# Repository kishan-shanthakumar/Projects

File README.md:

# Projects
The directory name is the tool/topic of the project.

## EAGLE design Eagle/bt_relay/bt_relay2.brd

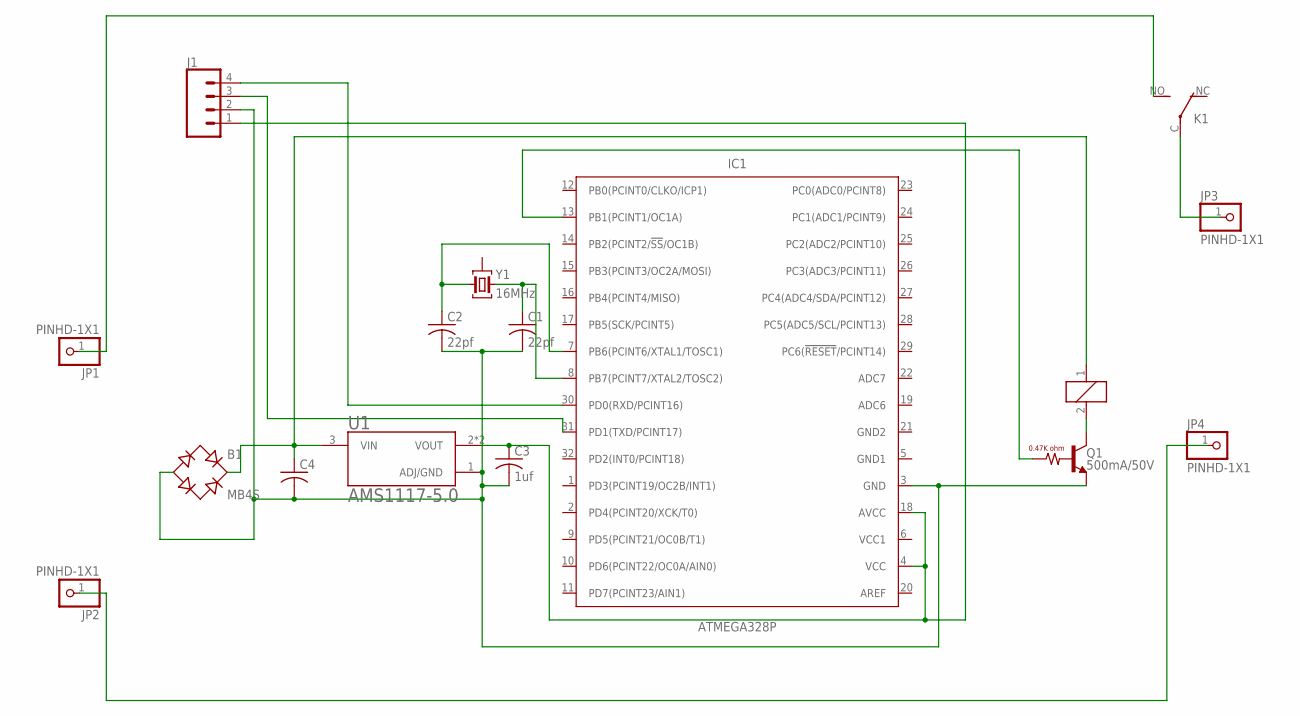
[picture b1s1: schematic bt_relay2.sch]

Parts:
B1: MB4S; SOIC-4
C1, C2: 22pf; C0402
C3: 1uf; C0402
C4: C-USC0402; C0402
IC1: ATMEGA328P; QFN50P500X500X90-33T310N
J1: CONN_04; 1X04
JP1, JP2, JP3, JP4: PINHD-1X1; 1X01
K1: CP1SA-12V; CP1SA
Q1: 500mA/50V; SOT23-3
U1: AMS1117-5.0; SOT229P700X180-4N
Y1: 16MHz; CRYSTAL_CMR200TB

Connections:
AREF: IC1.20 (AREF)
unnamed: C3.1, IC1.4 (VCC), IC1.18 (AVCC), J1.1, U1.2 (VOUT), U1.4 (VOUT)
unnamed: B1.-, C1.2, C2.2, C3.2, C4.2, IC1.3 (GND), J1.2, Q1.2 (E), U1.1 (ADJ/GND)
unnamed: B1.+, C4.1, K1.1, U1.3 (VIN)
unnamed: K1.2, Q1.3 (C)
unnamed: C2.1, IC1.7 (PB6(PCINT6/XTAL1/TOSC1)), Y1.1
unnamed: C1.1, IC1.8 (PB7(PCINT7/XTAL2/TOSC2)), Y1.2
unnamed: IC1.13 (PB1(PCINT1/OC1A)), Q1.1 (B)
unnamed: JP3.1, K1.C
unnamed: JP1.1, K1.NO (S)
unnamed: JP2.1, JP4.1
unnamed: IC1.30 (PD0(RXD/PCINT16)), J1.4
unnamed: IC1.31 (PD1(TXD/PCINT17)), J1.3
VCC1: IC1.6 (VCC1)

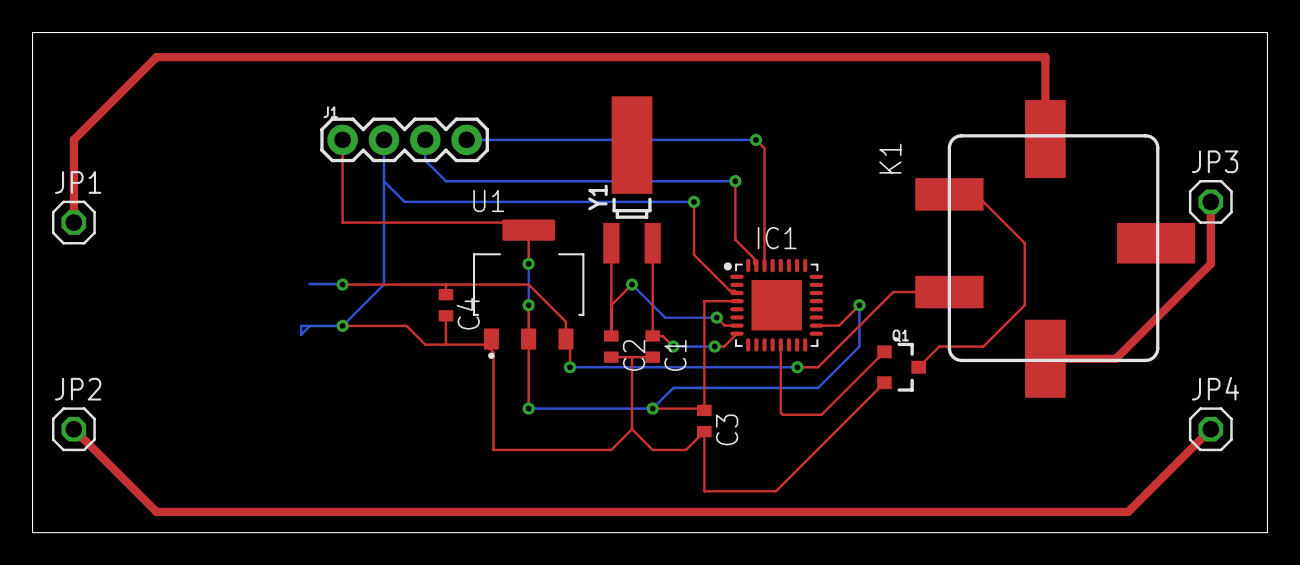
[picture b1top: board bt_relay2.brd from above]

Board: 2 copper layers, 75.9 x 30.7 mm, 15 parts (1 on the bottom side), 12 nets.

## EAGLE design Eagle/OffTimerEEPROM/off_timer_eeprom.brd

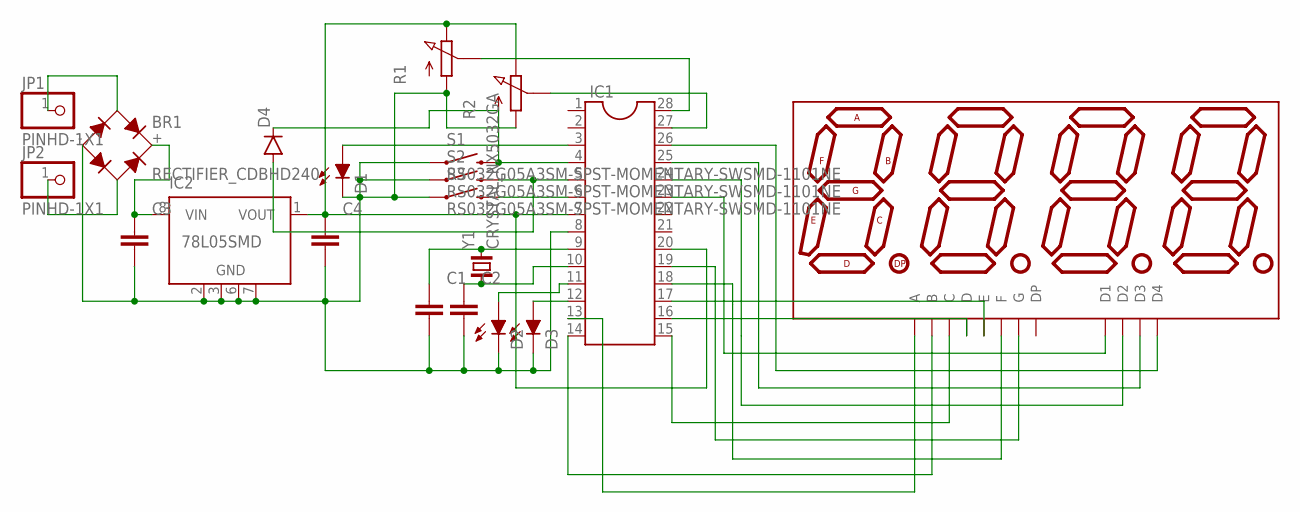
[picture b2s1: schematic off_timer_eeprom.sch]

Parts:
BR1: RECTIFIER_CDBHD240; RECTIFIER_TO-269AA
C1, C2, C3, C4: C_CHIP-0805(2012-METRIC); CAPC2012X110
D1, D2, D3: LED_LEDCHIP-LED0603MP; LED_CHIP-LED0603MP
D4: DIODEDIODE-123FL; DIODE_SOD-123FL
DISP1: ATA8041AB; 7-SEGMENT-4DIGIT-20MM
IC1: DIL28-3
IC2: 78L05SMD; SO08
JP1, JP2: PINHD-1X1; 1X01
R1, R2: PC25
S1, S2, S3: RS032G05A3SM-SPST-MOMENTARY-SWSMD-1101NE; TACTILE-SWITCH-1101NE
Y1: CRYSTAL_NX5032GA; CRYSTAL_2-SMD-5X3

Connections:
unnamed: IC1.6, S3.2
unnamed: C1.1, IC1.9, Y1.2
unnamed: C2.1, IC1.10, Y1.1
unnamed: C4.1, IC1.7, IC1.20, IC2.1 (VOUT), R1.E, R2.E
unnamed: BR1.-, C1.2, C2.2, C3.2, C4.2, D1.C, D2.C, D3.C, IC1.8, IC2.2 (GND), IC2.3 (GND), IC2.6 (GND), IC2.7 (GND), R1.A, R2.A, S1.1, S2.1, S3.1
unnamed: D1.A, IC1.3
unnamed: BR1.+, C3.1, IC2.8 (VIN)
unnamed: D4.A, IC1.5, S2.2
unnamed: D4.C, IC1.4, S1.2
unnamed: D3.A, IC1.12
unnamed: D2.A, IC1.11
unnamed: DISP1.6 (D4), IC1.26
unnamed: DISP1.8 (D3), IC1.25
unnamed: IC1.28, R1.S
unnamed: IC1.27, R2.S
unnamed: DISP1.9 (D2), IC1.24
unnamed: DISP1.12 (D1), IC1.23
unnamed: DISP1.5 (G), IC1.19
unnamed: DISP1.10 (F), IC1.18
unnamed: DISP1.4 (C), IC1.15
unnamed: DISP1.1 (E), IC1.17
unnamed: DISP1.2 (D), IC1.16
unnamed: DISP1.7 (B), IC1.14
unnamed: DISP1.11 (A), IC1.13
unnamed: BR1.AC1 (A1), JP1.1
unnamed: BR1.AC2 (A2), JP2.1

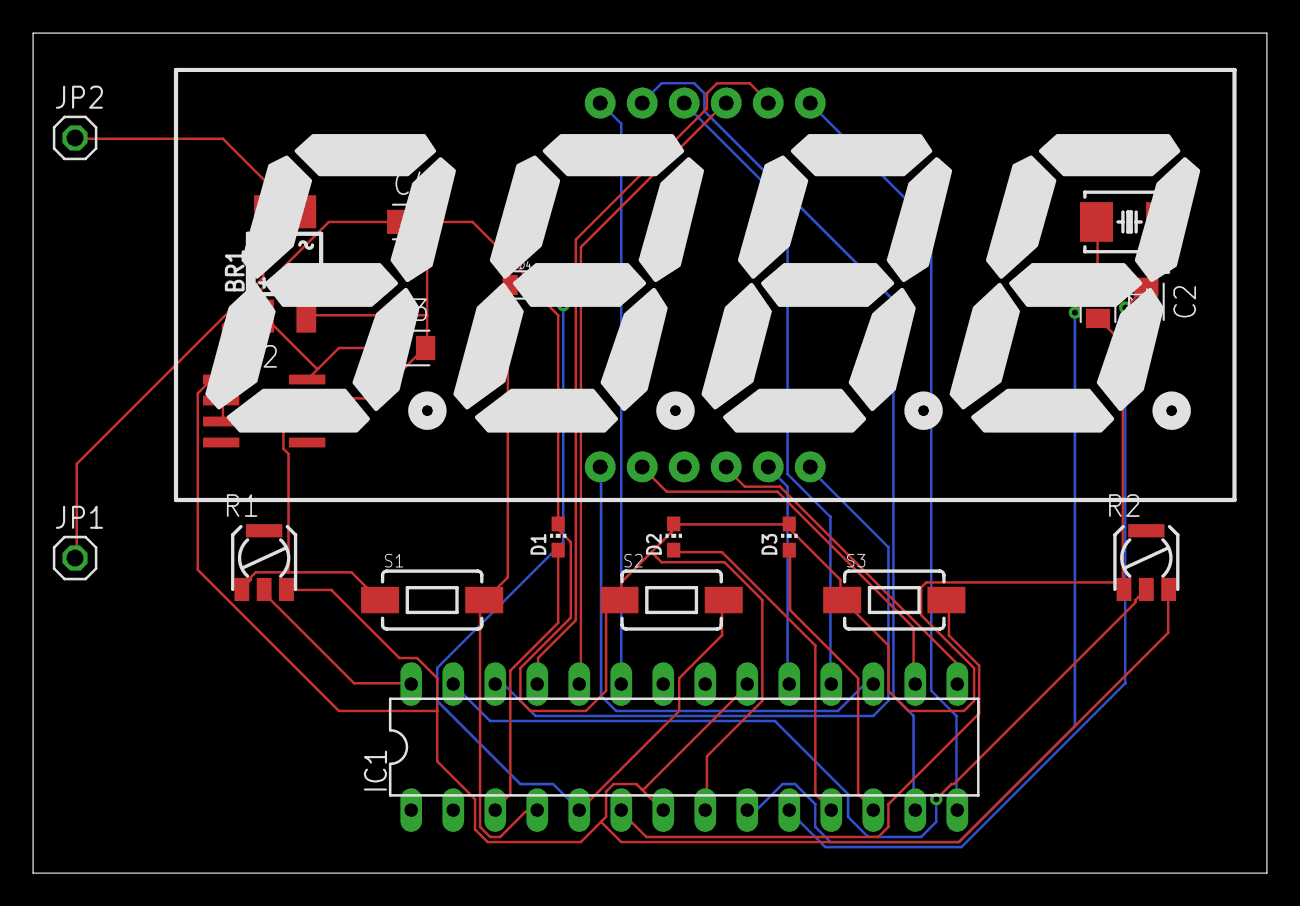
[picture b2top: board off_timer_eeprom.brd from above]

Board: 2 copper layers, 74.6 x 50.8 mm, 20 parts (0 on the bottom side), 26 nets.

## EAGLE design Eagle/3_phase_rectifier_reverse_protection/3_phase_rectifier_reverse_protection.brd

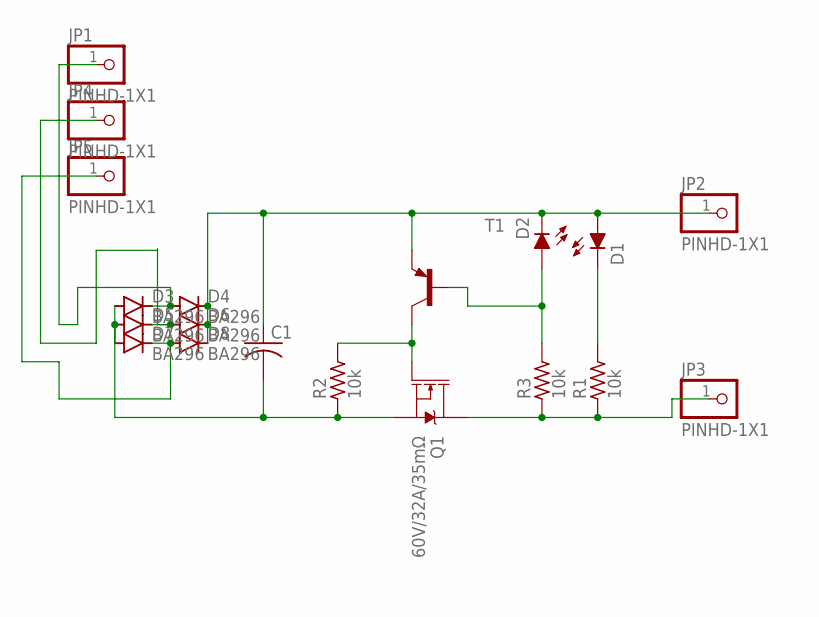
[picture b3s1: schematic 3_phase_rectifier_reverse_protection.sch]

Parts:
C1: C-US025-024X044; C025-024X044
D1, D2: LED_LEDCHIP-LED0603MP; LED_CHIP-LED0603MP
D3, D4, D5, D6, D7, D8: BA296; P2-15
JP1, JP2, JP3, JP4, JP5: PINHD-1X1; 1X01
Q1: 60V/32A/35mΩ; TO220V
R1, R2, R3: 10k; RC-MASTER-SMD_R0603MP
T1: -PNP-SC59-BEC; SC59-BEC

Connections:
GND: JP3.1, Q1.2 (D), R1.1, R3.1
unnamed: D3.C, D4.A, JP1.1
unnamed: Q1.1 (G), R2.2, T1.C
unnamed: D2.A, R3.2, T1.B
unnamed: D1.C, R1.2
unnamed: D5.C, D6.A, JP4.1
unnamed: D7.C, D8.A, JP5.1
unnamed: C1.2, D3.A, D5.A, D7.A, Q1.3 (S), R2.1
VCC: C1.1, D1.A, D2.C, D4.C, D6.C, D8.C, JP2.1, T1.E

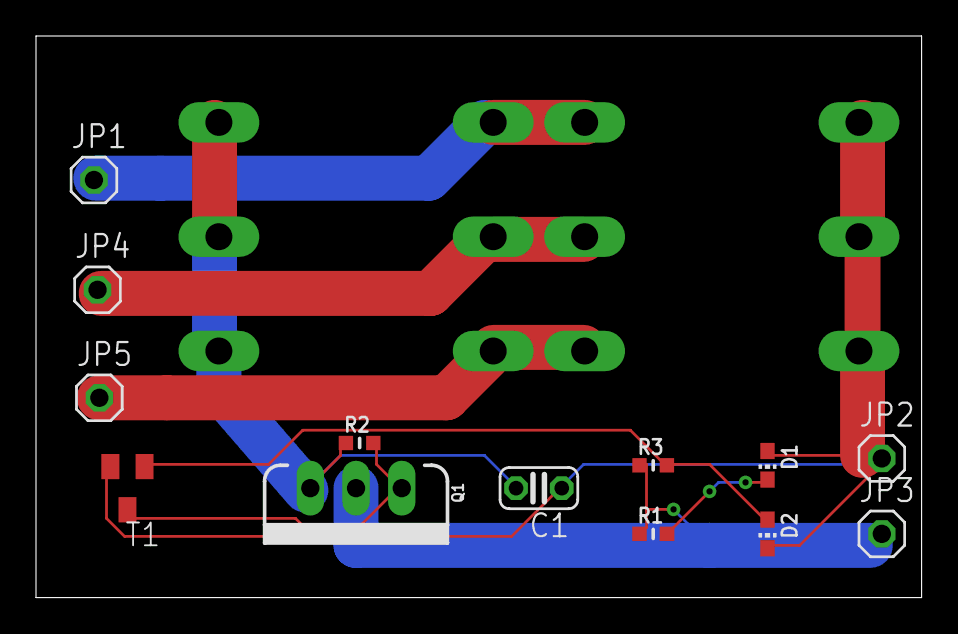
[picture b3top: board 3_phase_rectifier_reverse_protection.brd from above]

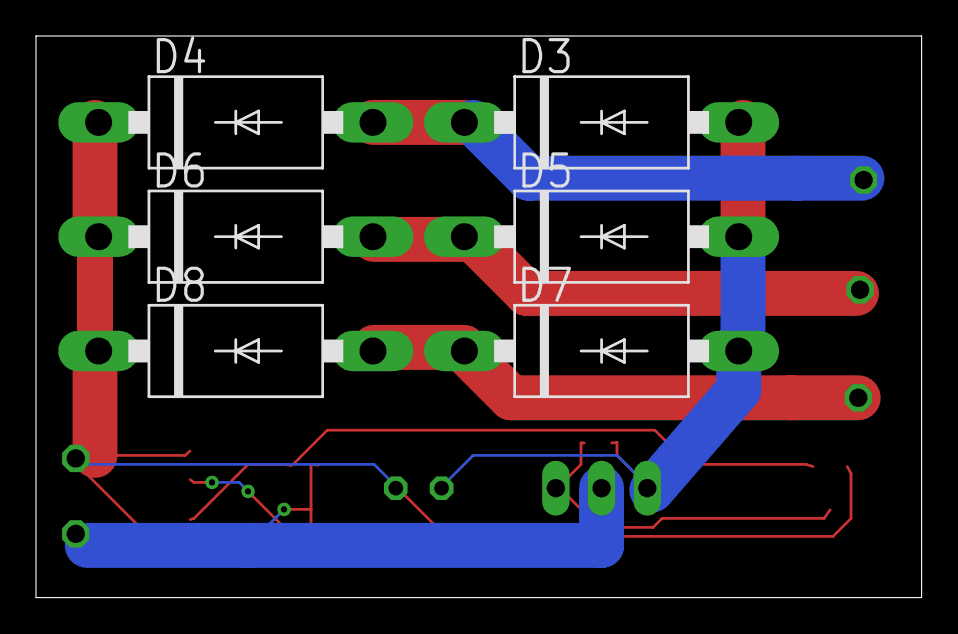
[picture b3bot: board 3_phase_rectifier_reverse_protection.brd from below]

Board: 2 copper layers, 49.2 x 31.2 mm, 19 parts (6 on the bottom side), 9 nets.

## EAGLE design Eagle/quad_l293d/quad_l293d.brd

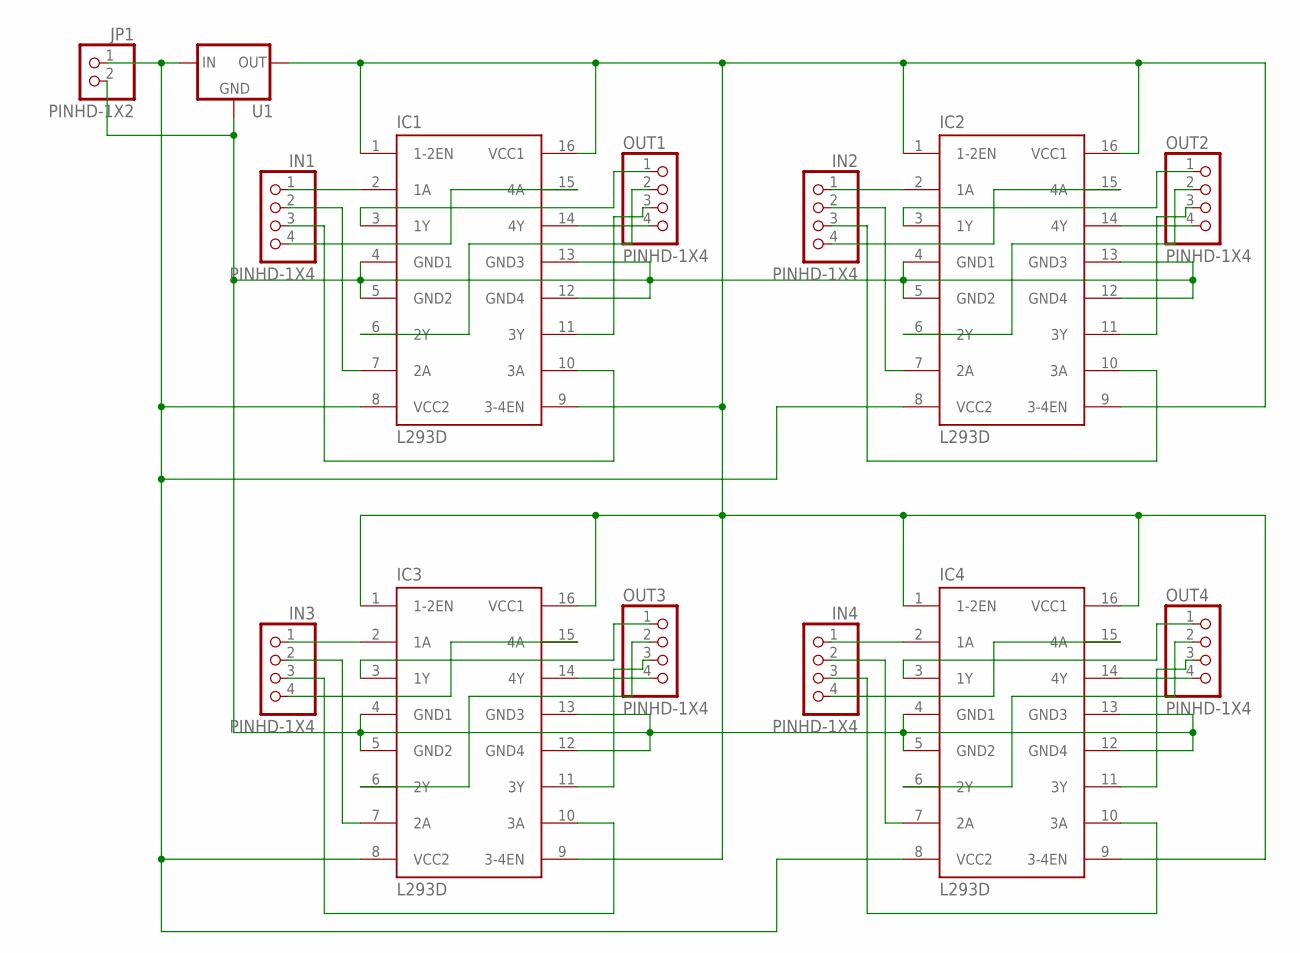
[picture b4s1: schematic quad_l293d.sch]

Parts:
IC1, IC2, IC3, IC4: L293D; DIL16
IN1, IN2, IN3, IN4: PINHD-1X4; 1X04
JP1: PINHD-1X2; 1X02
OUT1, OUT2, OUT3, OUT4: PINHD-1X4; 1X04
U1: V_REG_78XX-TO-220; TO-220-ALT

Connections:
GND: IC1.4 (GND1), IC1.5 (GND2), IC1.12 (GND4), IC1.13 (GND3), IC2.4 (GND1), IC2.5 (GND2), IC2.12 (GND4), IC2.13 (GND3), IC3.4 (GND1), IC3.5 (GND2), IC3.12 (GND4), IC3.13 (GND3), IC4.4 (GND1), IC4.5 (GND2), IC4.12 (GND4), IC4.13 (GND3), JP1.2, U1.GND
IN: IC1.8 (VCC2), IC2.8 (VCC2), IC3.8 (VCC2), IC4.8 (VCC2), JP1.1, U1.IN
unnamed: IC1.3 (1Y), OUT1.1
unnamed: IC1.14 (4Y), OUT1.4
unnamed: IC1.2 (1A), IN1.1
unnamed: IC1.7 (2A), IN1.2
unnamed: IC1.10 (3A), IN1.3
unnamed: IC1.15 (4A), IN1.4
unnamed: IC2.2 (1A), IN2.1
unnamed: IC2.7 (2A), IN2.2
unnamed: IC1.6 (2Y), OUT1.2
unnamed: IC1.11 (3Y), OUT1.3
unnamed: IC3.2 (1A), IN3.1
unnamed: IC2.10 (3A), IN2.3
unnamed: IC2.15 (4A), IN2.4
unnamed: IC2.3 (1Y), OUT2.1
unnamed: IC2.14 (4Y), OUT2.4
unnamed: IC2.6 (2Y), OUT2.2
unnamed: IC2.11 (3Y), OUT2.3
unnamed: IC3.7 (2A), IN3.2
unnamed: IC3.10 (3A), IN3.3
unnamed: IC3.15 (4A), IN3.4
unnamed: IC3.3 (1Y), OUT3.1
unnamed: IC3.14 (4Y), OUT3.4
unnamed: IC3.6 (2Y), OUT3.2
unnamed: IC3.11 (3Y), OUT3.3
unnamed: IC4.2 (1A), IN4.1
unnamed: IC4.7 (2A), IN4.2
unnamed: IC4.10 (3A), IN4.3
unnamed: IC4.15 (4A), IN4.4
unnamed: IC4.3 (1Y), OUT4.1
unnamed: IC4.14 (4Y), OUT4.4
unnamed: IC4.6 (2Y), OUT4.2
unnamed: IC4.11 (3Y), OUT4.3
OUT5V: IC1.1 (1-2EN), IC1.9 (3-4EN), IC1.16 (VCC1), IC2.1 (1-2EN), IC2.9 (3-4EN), IC2.16 (VCC1), IC3.1 (1-2EN), IC3.9 (3-4EN), IC3.16 (VCC1), IC4.1 (1-2EN), IC4.9 (3-4EN), IC4.16 (VCC1), U1.OUT

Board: 2 copper layers, 14 parts (0 on the bottom side), 35 nets, no tracks yet.

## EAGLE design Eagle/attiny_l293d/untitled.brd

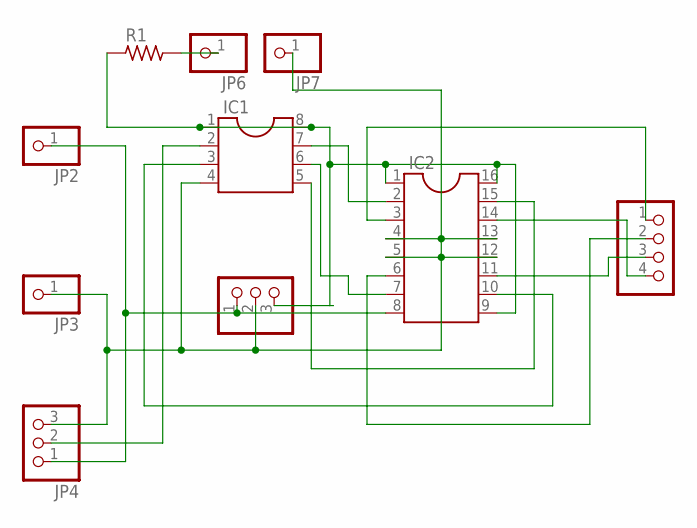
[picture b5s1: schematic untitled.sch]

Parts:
IC1: DIL8S; SOCKET-08
IC2: DIL16S; SOCKET-16
JP1: PINHD-1X4; 1X04
JP2, JP3, JP6, JP7: PINHD-1X1; 1X01
JP4, JP5: PINHD-1X3; 1X03
R1: RC-MASTER-SMD_R_0603MP; RC-MASTER-SMD_R0603MP

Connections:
GND: IC1.4, IC2.4, IC2.5, IC2.12, IC2.13, JP3.1, JP4.3, JP5.2, JP7.1
unnamed: IC2.3, JP1.1
unnamed: IC2.6, JP1.2
unnamed: IC1.2, JP4.2
unnamed: IC1.7, IC2.2
unnamed: IC1.6, IC2.7
unnamed: IC1.5, IC2.15
unnamed: IC1.3, IC2.10
unnamed: IC2.11, JP1.3
unnamed: IC2.14, JP1.4
unnamed: JP6.1, R1.2
V: IC1.1, IC1.8, IC2.1, IC2.9, IC2.16, JP5.3, R1.1
VDD: IC2.8, JP2.1, JP4.1, JP5.1

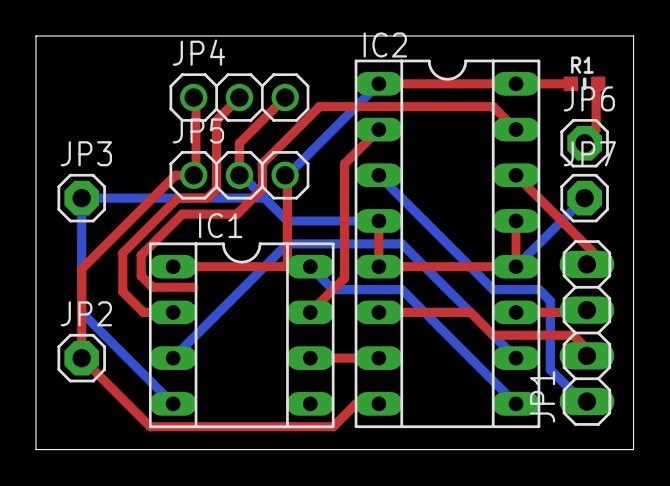
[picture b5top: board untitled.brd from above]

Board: 2 copper layers, 33.2 x 23.0 mm, 10 parts (0 on the bottom side), 13 nets.

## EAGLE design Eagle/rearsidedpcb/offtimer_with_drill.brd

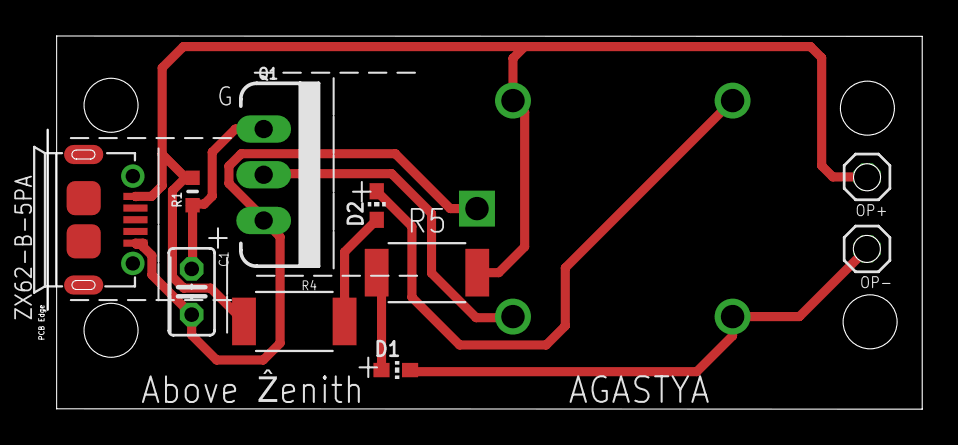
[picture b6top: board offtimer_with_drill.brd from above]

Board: 2 copper layers, 49.1 x 20.6 mm, 11 parts (1 on the bottom side), 8 nets.

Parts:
C1: C025-025X050
D1, D2: LED_CHIP-LED0603MP
OP+: 1X01
OP-: 1X01
Q1: 60V/32A/35mΩ; TO220V
R1: 1M; RC-MASTER-SMD_R0603MP
R4, R5: 10k; RESMELF5924
RELAY: JSM1-12V-5
USB1: ZX62-B-5PA; MICRO-USB5+6P-SMD-0.65-AB

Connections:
GND: C1.2, Q1.3, RELAY.1, USB1.5
unnamed: Q1.2, RELAY.5
unnamed: D1.C, OP-.1, RELAY.4
unnamed: C1.1, Q1.1, R1.1
unnamed: D1.A, R5.1
unnamed: D2.A, R4.1
unnamed: D2.C, RELAY.3
VBUS: OP+.1, R1.2, R4.2, R5.2, RELAY.2, USB1.1

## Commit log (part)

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2022-02-14 All Projects
2022-02-27 NRF24L01 implementation
2022-02-27 Started riscv core
2022-02-27 Opencl Implementation of Linear Regression
2022-03-02 TCL file for bit8alubehav for openlane
2022-03-04 Complete RV32I core with 2d reg unchecked
2022-03-04 Corrected syntax errors
2022-03-04 Added write and read function in harvard architecture
2022-03-04 Added trap support
2022-03-04 Corrected s type and l type functional errors
2022-03-04 Corrected 2d reg definition
2022-03-05 config file for rv32i verilog file in openlane
2022-03-05 Corrected sign extension errors
2022-03-06 Corrected runtime errors
2022-03-06 Corrected 32 bit word read
2022-03-06 Address for branch
2022-03-08 Corrected 1 bit error and signed numbers
2022-03-16 Started rv32i soc design
2022-03-16 Basic definition of rv32i soc
2022-03-16 Added cache and improvements
2022-03-17 Added peripheral modules
2022-03-17 Defined sub-modules for peripherals
2022-03-20 Added ports for vga output
2022-03-20 Modified vga_controller to suit addressless data processing
2022-03-20 Correction: Removed address field and incrementation
2022-03-20 Reinserted memory address for adding support for independent memory
2022-03-22 Matching input and output widths
2022-03-22 Added UART_tx
2022-03-22 Added comments pointers
2022-03-22 Deleted SPI
2022-03-23 Removed unnecessary files
2022-04-11 Added waiting for mem op
2022-04-11 Removed redundant op before wait stage
2022-04-11 riscv_core.v: Furthur changes to 1 cycle delay of mem op
2022-04-11 risc_core.v: Added one more cycle to mem write op
2022-06-02 Added torch stand for custom torch
2022-06-12 Created bsv folder
2022-06-14 WIP parametric MAC unit
2022-07-05 Adding an example for reference
2022-07-05 WIP parametrized MAC unit
2022-07-06 Fixed bugs
2022-07-06 WIP: corrected macro definition
2022-07-27 Corrected redundant definitions
2022-07-27 Corrected incorrect definition of add module
2022-07-27 Removed peripheral files
2022-07-27 Added gitignore file
2022-07-27 Removed traces of SoC
2022-07-31 Initial commit sha_256
2022-07-31 WIP sha 256
2022-09-25 BCH 63,57
2022-09-25 Correction
2022-10-08 Fixes
2022-10-11 TODOs of DSD
2022-10-11 Cleanup
2022-10-11 Added new files
2022-10-12 Gate counter in synthesized files
2022-10-14 sequential elements todo
2022-10-18 Incomplete mock assignment
2022-10-18 FALU initial commit
2022-10-18 Corrected cseladd, finished stage 1 of fadd
2022-10-19 Added stage 2 and part of stage 3
2022-10-22 Iterative comp
2022-10-22 TODO: different sign numbers, with negative index
2022-10-25 Major cleanup, TODO: mis-matching signed numbers
2022-10-25 Added same exp check
2022-10-25 Cleanup for processor
2022-10-25 Added newton raphson method
2022-10-27 TODO: unequal exponents subtraction
2022-10-28 Initial structure for fmul
2022-10-28 fmul added mul modules
2022-10-28 Changed bias hardcoding
2022-10-28 TODO: Simulation
2022-10-29 TODO: exp calc verification
2022-10-29 Finished fmul
2022-10-29 prelim design for fdiv
2022-10-29 Corrected the module name
2022-10-30 Renamed file name ndiv to n_divider
2022-10-30 Modified divider
2022-10-31 Changed nomenclature
2022-11-05 Added testbench
2022-11-05 Corrected design and added delay in tb
2022-11-05 Changed shifter logic
2022-11-05 Finished fdiv, todo resolution
2022-11-05 Added 0 assignment
2022-11-05 Changed the length of the shift amount
2022-11-06 Changed from pipelined structure to combi
2022-11-06 Changed resolution
2022-11-06 Created falu
2022-11-07 Seperated out enc_n module
2022-11-07 Corrected errors in fadd
2022-11-07 Expt changes. No reason. Hardcoding
2022-11-10 Added prev version for assignment
2022-11-17 Whatsapp spam
2022-11-19 Assignment required changes
2022-11-23 Corrected ready working
2022-11-23 Syn corrections
2022-11-24 Output only when ready is asserted, default ready_st to 0
2022-11-24 ready error
2022-11-25 Added special cases support
2022-11-25 Changes to remove all errors about latches and non combinational logic in always_comb
2022-11-25 Meeting timing requirements
2022-11-26 corrected unused error for outba and renamed file
2022-11-27 Handling of warnings
2022-11-27 Additional warnings
2022-11-27 verilator warnings
2022-12-02 Changed the states functionality
2022-12-02 Randomised testbench
2022-12-02 Added a and b loggers
2022-12-04 Behavioural fadd16, required corner case normalisation
2022-12-05 Corrected bit errors
2022-12-05 Randomised tb for falu
2022-12-05 syntax error
2022-12-05 Changes to accomodate checking
2022-12-05 Corrected errors
2022-12-06 Changes to assignment
2022-12-06 Added start and end log
2022-12-06 Additional corrections
2022-12-06 Corrections to diff exp sub
2022-12-06 Removed behavioural version
2022-12-06 correction in subtraction
2022-12-06 Increased cases and logging hex values
2022-12-06 Added diff exp add corrections
2022-12-07 Testbench for fadd
2022-12-07 Added loggers for start and end
2022-12-07 Corrected latching error
2022-12-07 proper assign for out and changing bit width
2022-12-07 added result bit for tb
2022-12-07 check bits and randomised
2022-12-07 Simpler Logic
2022-12-07 Added special cases and corrected exp
2022-12-07 Added special cases
2022-12-07 bit correction
2022-12-07 Different alus
2022-12-07 renaming of module
2022-12-07 Changes to the divider
2023-01-02 VGA controller with display blank
2023-01-02 VGA controller 24 bit
2023-01-03 risc v core corrections
2023-01-03 Corrections
2023-01-03 parallel bubble sort init
2023-01-07 Fdiv completed
2023-01-07 Parametrisation of exponent checking
2023-01-07 Special cases
2023-01-07 special case same numbers
2023-01-07 Correcting inconsistencies
2023-01-08 async reset for mem_test
2023-01-08 removed redundant file
2023-01-08 the short mem inst
2023-01-08 barrel_shifter sv
2023-01-09 TODO: yet to add riscv core
2023-01-13 Changed 1 to 1'b1
2023-02-02 Added delays for read, write, jump, branch
2023-02-14 sapinsky_triangle
2023-02-18 Added special characters
2023-04-13 Removed old file
2023-04-29 Coursework
2024-02-05 project files
2024-02-09 minor fix, updates
2024-02-09 run fix
2024-02-09 print values
2024-02-09 constant reading
2024-02-09 pres to alt
2024-02-09 syntax cleanup
2024-02-09 numerical correction
2024-02-09 correction for ln
2024-02-09 10ms delay
2024-02-10 add plotter on exit
2024-02-10 subplots
2024-02-10 temp change
2024-02-10 removed print
2024-02-10 print len
2024-02-10 line break
2024-02-10 0 return for check
2024-02-10 file logging
2024-02-10 minor cleanup
2024-02-10 logs folder
2024-02-10 remove time reset
2024-02-10 extra time for file op
2024-02-11 changed details
2024-02-11 changed reading format
2024-02-11 default tk layout
2024-02-11 temp changes
2024-02-11 undo changes
2024-02-12 real time sensor update
2024-02-12 syntax changes
2024-02-12 print log
2024-02-12 minor fix
2024-02-12 added units
2024-02-12 syntax fix
2024-02-12 code cleanup
2024-02-12 changes to data read
2024-02-12 diff config
2024-02-13 added scrolling
2024-02-13 syntax
2024-02-13 moved frames inside canvas
2024-02-13 canvas resize
2024-02-13 change canvas
2024-02-13 second frame
2024-02-13 add xscroll
2024-02-13 reframe window
2024-02-13 apply canvas width
2024-02-13 reframe canvas
2024-02-13 tabbed window
2024-02-13 change tab
2024-02-13 tab fix
2024-02-13 rename tab
2024-02-13 rewrite canvas
2024-02-13 removed canvas fill
2024-02-13 resize canvas
2024-02-14 added mcp read
2024-02-14 continuous run
2024-02-14 value read function
2024-02-14 check di
2024-02-14 init delay
2024-02-14 continous print of values
2024-02-14 buffer current di
2024-02-15 moving to rf transmitter
2024-02-15 filename for log
2024-02-15 logging interface
2024-02-15 return filename
2024-02-15 graceful error handling
2024-02-15 changed mode of the log open
2024-02-15 restore window to tk
2024-02-15 exist ok true for logs
2024-02-15 syntax change
2024-02-15 log time
2024-02-15 csv format indendation
2024-02-15 different mpu library
2024-02-15 added except print messages
2024-02-15 added print in mpu library
2024-02-15 change
2024-02-15 added calibration for mpu
2024-02-15 calibration constant
2024-02-15 logic error correction
2024-02-15 proper mean calc
2024-02-15 post processing data
2024-02-15 retained previous values
2024-02-15 re-order updation
2024-02-15 added delay
2024-02-15 mean of mpu values
2024-02-15 fix errors
2024-02-15 fix calibration constants
2024-02-15 increased delay
2024-02-15 round deciaml places
2024-02-15 referencing di obj
2024-02-15 removing cal consts
2024-02-15 re -introduced cal const
2024-02-15 truncating gyro val
2024-02-16 orientation based calibration
2024-02-16 calibration change
2024-02-16 calibration fix
2024-02-16 changed from gps to glonass
2024-02-16 gps logging
2024-02-16 gps changes
2024-02-16 try catch
2024-02-16 re-init
2024-02-16 split data checking
2024-02-16 implicit init gps ser
2024-02-16 added gps msg print
2024-02-16 better logging
2024-02-16 temp print statement
2024-02-16 move print statement
2024-02-16 logical error fix
2024-02-16 added units to altitude
2024-02-22 removed velocity calculation
2024-02-28 added gps signal validity
2024-03-17 gps verbose data
2024-03-17 try except for gps verbose
2024-03-17 moved data logging and change data type
2024-03-17 data return change
2024-03-17 log change
2024-03-17 using original source
2024-03-17 data read format
2024-03-17 changed updation rate of gps
2024-03-17 function cal l fix
2024-03-17 if condition to skip recursion
2025-02-19 recent designs
2025-04-28 designs
2025-06-16 swing_plant_pot

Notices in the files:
parts and their libraries:
SparkFun-DiscreteSemi: Licensing: Creative Commons ShareAlike 4.0 International - https://creativecommons.org/licenses/by-sa/4.0
